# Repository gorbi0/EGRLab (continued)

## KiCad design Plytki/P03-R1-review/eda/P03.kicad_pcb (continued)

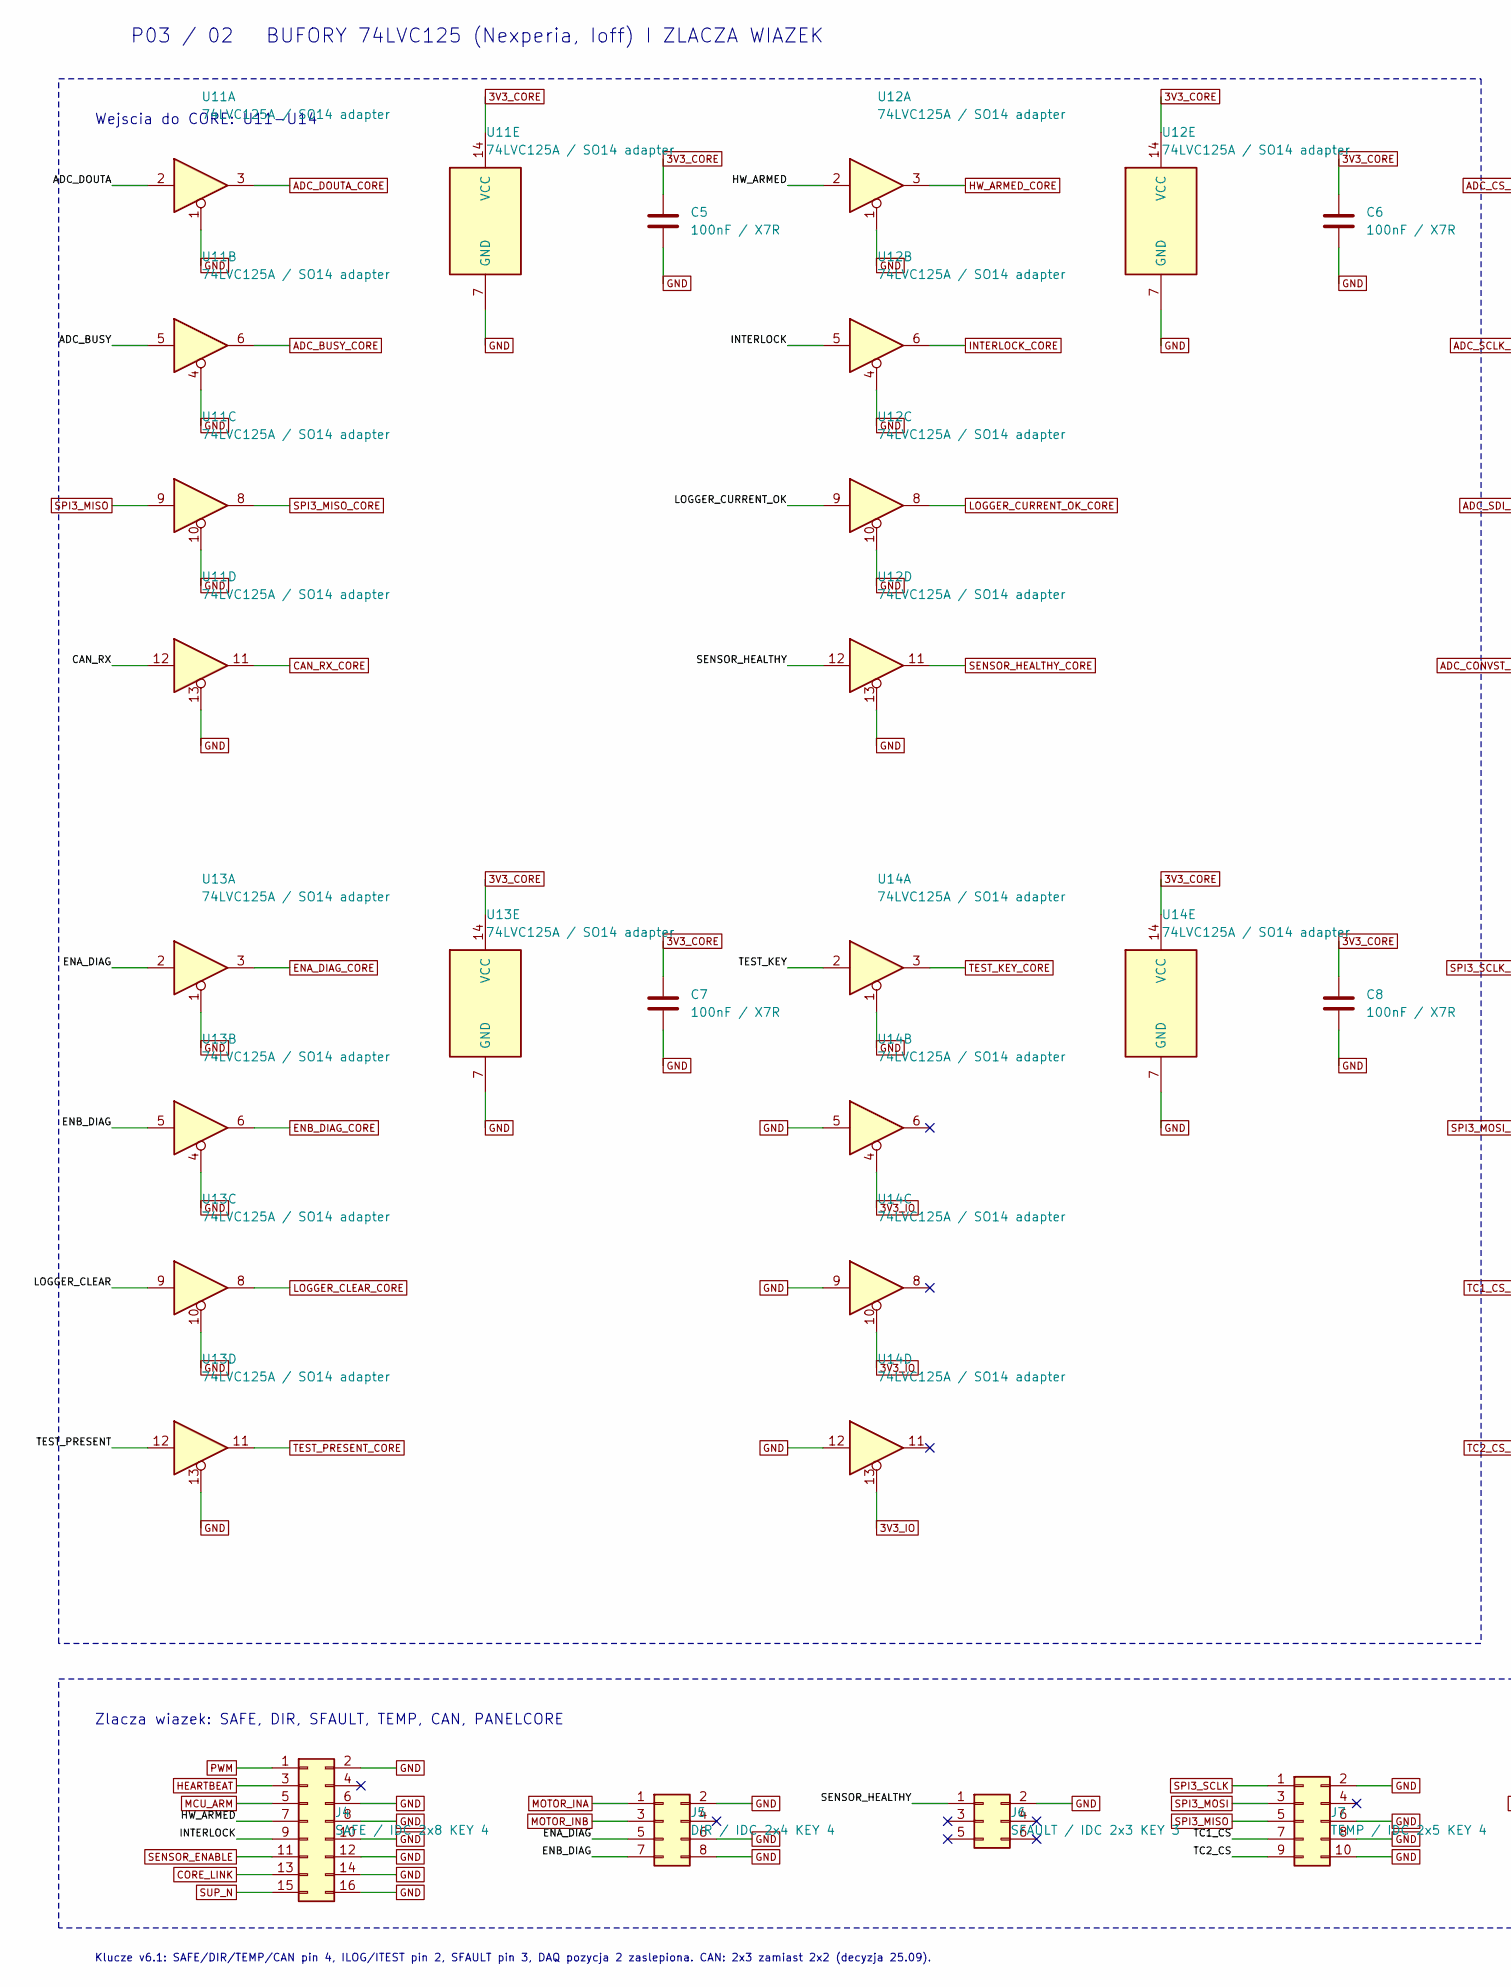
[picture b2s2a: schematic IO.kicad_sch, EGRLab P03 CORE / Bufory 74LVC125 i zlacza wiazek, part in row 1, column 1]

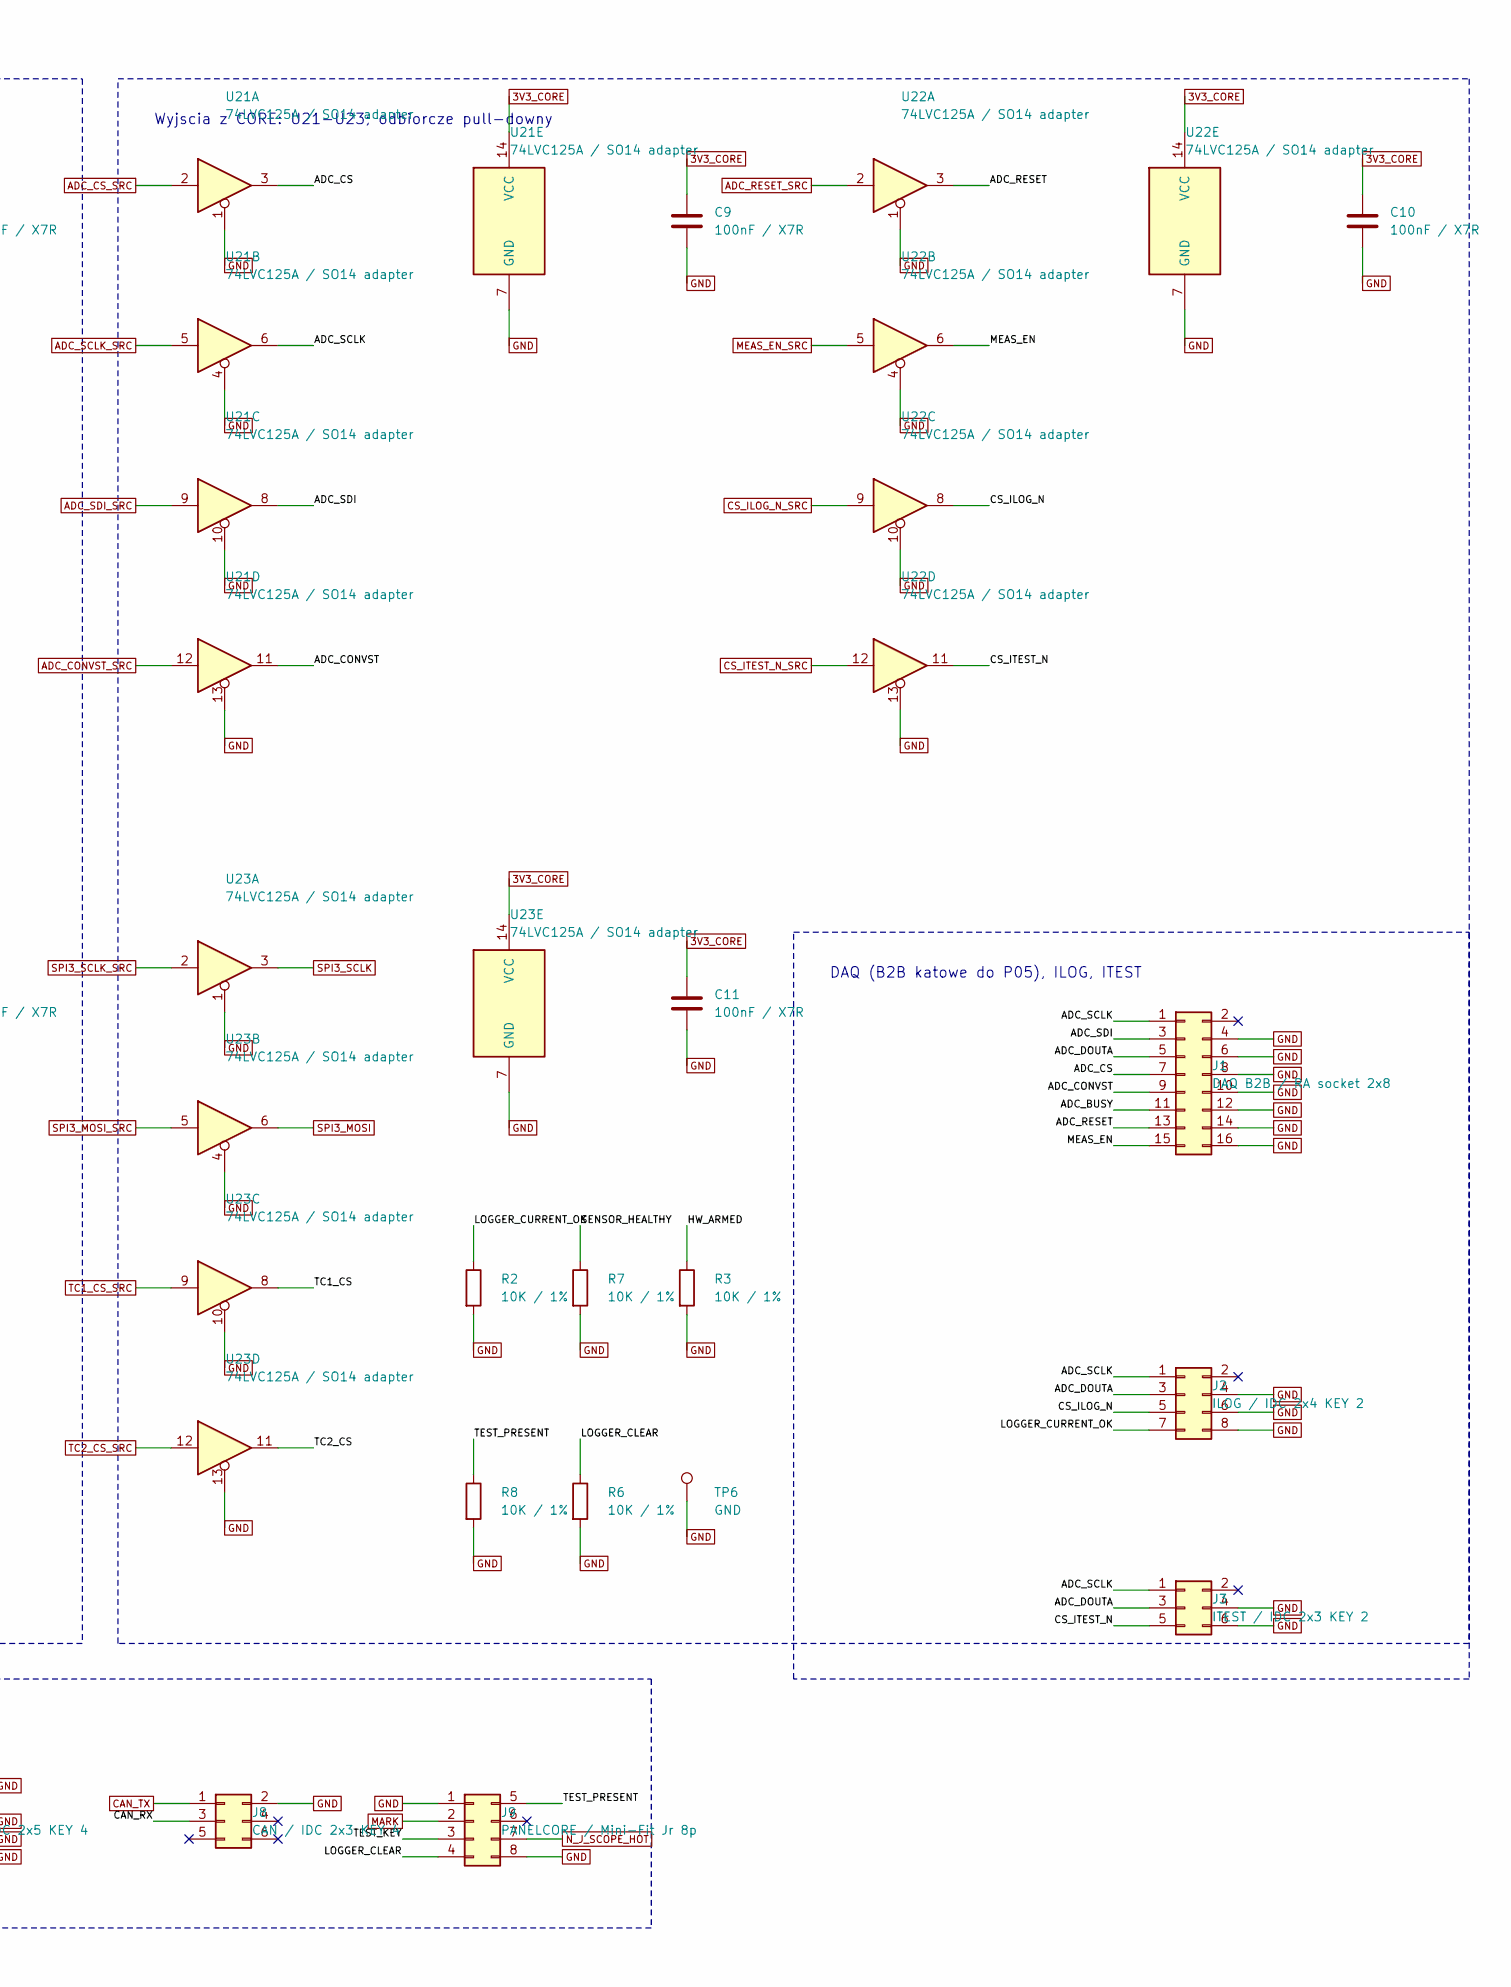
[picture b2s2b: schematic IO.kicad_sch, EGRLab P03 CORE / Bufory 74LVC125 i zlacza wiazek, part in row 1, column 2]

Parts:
C5, C6, C7, C8, C9, C10, C11: 100nF / X7R; C_Vishay_K15_H5_P5; MPN K104K15X7RF53H5
J1: DAQ B2B / RA socket 2x8; PinSocket_2x08_P2.54mm_Horizontal; MPN Samtec SSW-108-02-G-D-RA (right-angle 2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
J2: ILOG / IDC 2x4 KEY 2; IDC-Header_2x04_P2.54mm_Vertical; MPN IDC box header 2x4, 2.54 mm, Au
J3: ITEST / IDC 2x3 KEY 2; IDC-Header_2x03_P2.54mm_Vertical; MPN IDC box header 2x3, 2.54 mm, Au
J4: SAFE / IDC 2x8 KEY 4; IDC-Header_2x08_P2.54mm_Vertical; MPN IDC box header 2x8, 2.54 mm, Au
J5: DIR / IDC 2x4 KEY 4; IDC-Header_2x04_P2.54mm_Vertical; MPN IDC box header 2x4, 2.54 mm, Au
J6: SFAULT / IDC 2x3 KEY 3; IDC-Header_2x03_P2.54mm_Vertical; MPN IDC box header 2x3, 2.54 mm, Au
J7: TEMP / IDC 2x5 KEY 4; IDC-Header_2x05_P2.54mm_Vertical; MPN IDC box header 2x5, 2.54 mm, Au
J8: CAN / IDC 2x3 KEY 4; IDC-Header_2x03_P2.54mm_Vertical; MPN IDC box header 2x3, 2.54 mm, Au
J9: PANELCORE / Mini-Fit Jr 8p; Molex_Mini-Fit_Jr_5566-08A_2x04_P4.20mm_Vertical; MPN Molex Mini-Fit Jr 5566-08A vertical, Au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
R2, R3, R6, R7, R8: 10K / 1%; R_Axial_DIN0207_L6.3mm_D2.5mm_P10.16mm_Horizontal; MPN MF0207FTE-10K
TP6: GND; TestPad_1; MPN PCB test pad
U11, U12, U13, U14, U21, U22, U23: 74LVC125A / SO14 adapter; Adapter_SO14_DIP14_W15.24_Kamami575068; MPN 74LVC125AD,118 (Nexperia) on Kamami 575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

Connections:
3V3_CORE: C5.1, C6.1, C7.1, C8.1, C9.1, C10.1, C11.1, U11.14 (VCC), U12.14 (VCC), U13.14 (VCC), U14.14 (VCC), U21.14 (VCC), U22.14 (VCC), U23.14 (VCC); also elsewhere on the board
3V3_IO: U14.4, U14.10, U14.13; also elsewhere on the board
/IO/ADC_BUSY: J1.11, U11.5
/IO/ADC_CONVST: J1.9, U21.11
/IO/ADC_CS: J1.7, U21.3
/IO/ADC_DOUTA: J1.5, J2.3, J3.3, U11.2
/IO/ADC_RESET: J1.13, U22.3
/IO/ADC_SCLK: J1.1, J2.1, J3.1, U21.6
/IO/ADC_SDI: J1.3, U21.8
/IO/CAN_RX: J8.3, U11.12
/IO/CS_ILOG_N: J2.5, U22.8
/IO/CS_ITEST_N: J3.5, U22.11
/IO/ENA_DIAG: J5.5, U13.2
/IO/ENB_DIAG: J5.7, U13.5
/IO/HW_ARMED: J4.7, R3.1, U12.2
/IO/INTERLOCK: J4.9, U12.5
/IO/LOGGER_CLEAR: J9.4, R6.1, U13.9
/IO/LOGGER_CURRENT_OK: J2.7, R2.1, U12.9
/IO/MEAS_EN: J1.15, U22.6
/IO/SENSOR_HEALTHY: J6.1, R7.1, U12.12
/IO/TC1_CS: J7.7, U23.8
/IO/TC2_CS: J7.9, U23.11
/IO/TEST_KEY: J9.3, U14.2
/IO/TEST_PRESENT: J9.5, R8.1, U13.12
ADC_BUSY_CORE: U11.6; also elsewhere on the board
ADC_CONVST_SRC: U21.12; also elsewhere on the board
ADC_CS_SRC: U21.2; also elsewhere on the board
ADC_DOUTA_CORE: U11.3; also elsewhere on the board
ADC_RESET_SRC: U22.2; also elsewhere on the board
ADC_SCLK_SRC: U21.5; also elsewhere on the board
ADC_SDI_SRC: U21.9; also elsewhere on the board
CAN_RX_CORE: U11.11; also elsewhere on the board
CAN_TX: J8.1; also elsewhere on the board
CORE_LINK: J4.13; also elsewhere on the board
CS_ILOG_N_SRC: U22.9; also elsewhere on the board
CS_ITEST_N_SRC: U22.12; also elsewhere on the board
ENA_DIAG_CORE: U13.3; also elsewhere on the board
ENB_DIAG_CORE: U13.6; also elsewhere on the board
GND: C5.2, C6.2, C7.2, C8.2, C9.2, C10.2, C11.2, J1.4, J1.6, J1.8, J1.10, J1.12, J1.14, J1.16, J2.4, J2.6, J2.8, J3.4, J3.6, J4.2, J4.6, J4.8, J4.10, J4.12, J4.14, J4.16, J5.2, J5.6, J5.8, J6.2, J7.2, J7.6, J7.8, J7.10, J8.2, J9.1, J9.8, R2.2, R3.2, R6.2, R7.2, R8.2, TP6.1, U11.1, U11.4, U11.7 (GND), U11.10, U11.13, U12.1, U12.4, U12.7 (GND), U12.10, U12.13, U13.1, U13.4, U13.7 (GND), U13.10, U13.13, U14.1, U14.5, U14.7 (GND), U14.9, U14.12, U21.1, U21.4, U21.7 (GND), U21.10, U21.13, U22.1, U22.4, U22.7 (GND), U22.10, U22.13, U23.1, U23.4, U23.7 (GND), U23.10, U23.13; also elsewhere on the board
HEARTBEAT: J4.3; also elsewhere on the board
HW_ARMED_CORE: U12.3; also elsewhere on the board
INTERLOCK_CORE: U12.6; also elsewhere on the board
LOGGER_CLEAR_CORE: U13.8; also elsewhere on the board
LOGGER_CURRENT_OK_CORE: U12.8; also elsewhere on the board
MARK: J9.2; also elsewhere on the board
MCU_ARM: J4.5; also elsewhere on the board
MEAS_EN_SRC: U22.5; also elsewhere on the board
MOTOR_INA: J5.1; also elsewhere on the board
MOTOR_INB: J5.3; also elsewhere on the board
N_J_SCOPE_HOT: J9.7; also elsewhere on the board
PWM: J4.1; also elsewhere on the board
SENSOR_ENABLE: J4.11; also elsewhere on the board
SENSOR_HEALTHY_CORE: U12.11; also elsewhere on the board
SPI3_MISO: J7.5, U11.9; also elsewhere on the board
SPI3_MISO_CORE: U11.8; also elsewhere on the board
SPI3_MOSI: J7.3, U23.6; also elsewhere on the board
SPI3_MOSI_SRC: U23.5; also elsewhere on the board
SPI3_SCLK: J7.1, U23.3; also elsewhere on the board
SPI3_SCLK_SRC: U23.2; also elsewhere on the board
SUP_N: J4.15; also elsewhere on the board
TC1_CS_SRC: U23.9; also elsewhere on the board
TC2_CS_SRC: U23.12; also elsewhere on the board
TEST_KEY_CORE: U14.3; also elsewhere on the board
TEST_PRESENT_CORE: U13.11; also elsewhere on the board

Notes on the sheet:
P03 / 02 BUFORY 74LVC125 (Nexperia, Ioff) I ZLACZA WIAZEK
Wejscia do CORE: U11-U14
Wyjscia z CORE: U21-U23; odbiorcze pull-downy
DAQ (B2B katowe do P05), ILOG, ITEST
Zlacza wiazek: SAFE, DIR, SFAULT, TEMP, CAN, PANELCORE
Klucze v6.1: SAFE/DIR/TEMP/CAN pin 4, ILOG/ITEST pin 2, SFAULT pin 3, DAQ pozycja 2 zaslepiona. CAN: 2x3 zamiast 2x2 (decyzja 25.09).

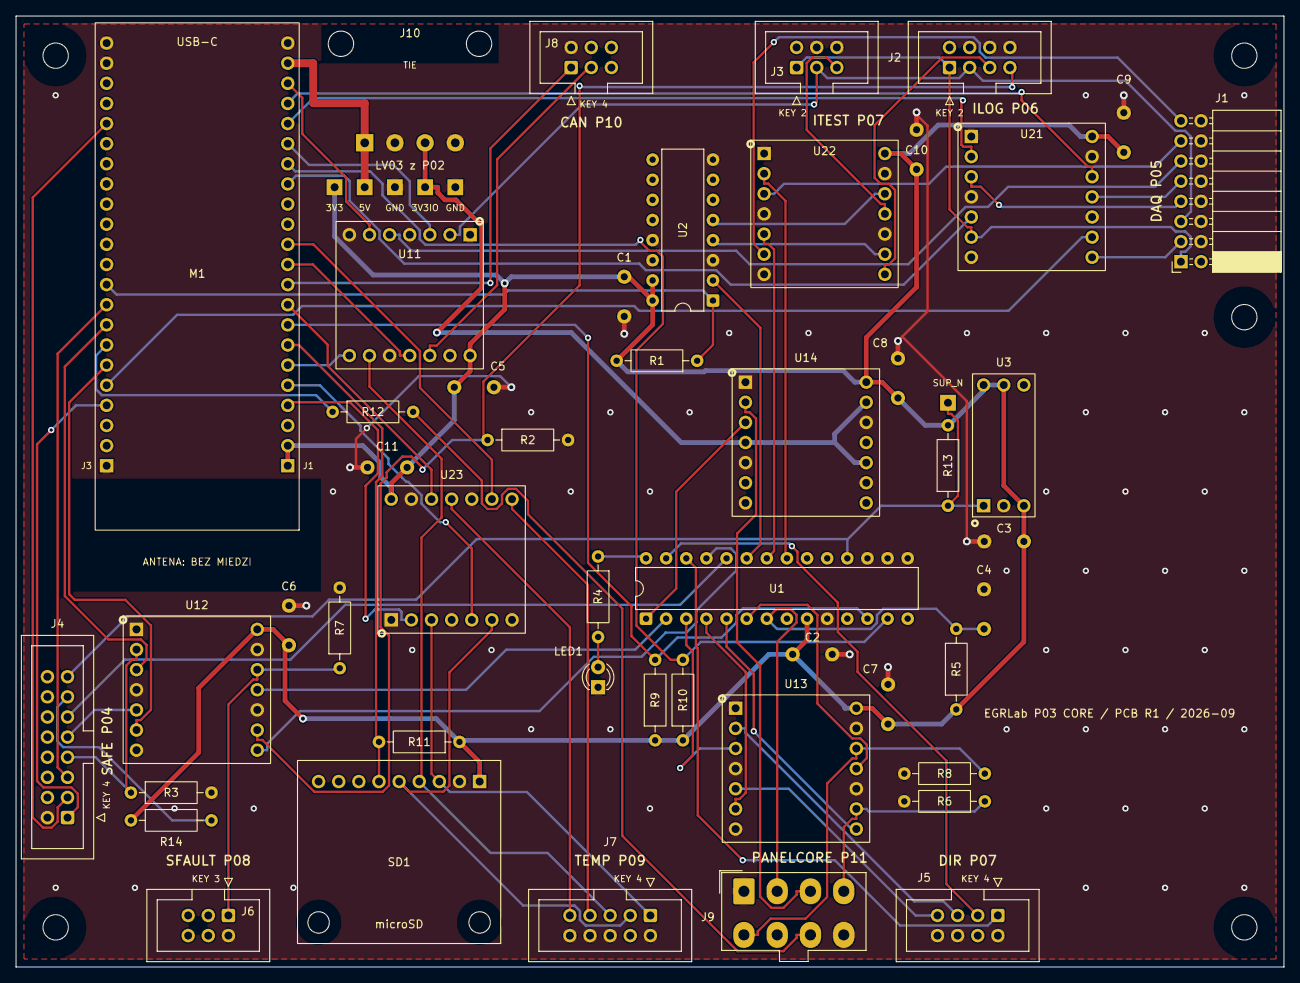
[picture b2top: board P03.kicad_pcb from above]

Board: 2 copper layers, 160.0 x 120.0 mm, 59 parts (0 on the bottom side), 73 nets.

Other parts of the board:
H1, H2, H3, H4, H5: M3 NPTH

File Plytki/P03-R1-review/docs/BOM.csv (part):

ref;source_ref;display;mpn;qty;footprint;url;note
M1;M1;Waveshare ESP32-S3-DEV-KIT-N32R16V;owned (Waveshare ESP32-S3-DEV-KIT-N32R16V) on 2x 1x22 female headers;1;P03:Waveshare_ESP32-S3-DEV-KIT_2x22_W22.86;https://docs.waveshare.com/ESP32-S3-DEV-KIT-N8R8;"Rows 22.86 mm (measured). GPIO numbers are the v6.1 contract. Remove the on-board RGB LED on GPIO38 (v6.1). GPIO47/48 1.8 V: unused. 3V3 = 3V3_CORE; never tie to 3V3_IO."
SD1;SD1;Adafruit 4682 microSD (3V);Adafruit 4682 on a 1x9 female header + 2x M2.5 spacer;1;P03:Adafruit_4682_microSD_1x09;https://www.adafruit.com/product/4682;User decision 25.09: Adafruit 4682 (3 V only, no regulator/level shifter). SO = card out (MISO), SI = card in (MOSI). D1, DAT2, DET unused.
U1;U17;MCP23017-E/SP;MCP23017-E/SP;1;Package_DIP:DIP-28_W7.62mm;https://ww1.microchip.com/downloads/en/devicedoc/20001952c.pdf;Address 0x20 (A2..A0 = GND). IODIRA 0x10, IODIRB 0x7F (v6.1). In 2x DIP14 precision sockets end to end (bought).
C2;C_DEC_U17_9;100nF / X7R;K104K15X7RF53H5;1;P03:C_Vishay_K15_H5_P5;https://www.vishay.com/docs/45171/kseries.pdf;At U1 pin 9.
U2;U_CS;SN74HC139N;SN74HC139N;1;Package_DIP:DIP-16_W7.62mm;https://www.ti.com/lit/ds/symlink/sn74hc139.pdf;/G = GPIO38, A = MEAS_BANK, B = GND (v6.1). Second half disabled. DIP16 socket (bought).
C1;C_CS;100nF / X7R;K104K15X7RF53H5;1;P03:C_Vishay_K15_H5_P5;https://www.vishay.com/docs/45171/kseries.pdf;At U2 pin 16.
R1;R_CS_IDLE;10K / 1%;MF0207FTE-10K;1;Resistor_THT:R_Axial_DIN0207_L6.3mm_D2.5mm_P10.16mm_Horizontal;https://www.yageo.com/upload/media/product/productsearch/dat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;Decoder disabled while GPIO38 floats.
U3;U5;TPS3808G33DBVR / PA0085;TPS3808G33DBVR on Chip Quik PA0085;1;P03:Adapter_SOT23-6_DIP6_W15.24_ChipQuik_PA0085;https://www.ti.com/lit/ds/symlink/tps3808.pdf;SOT23-6 on PA0085 (rows 15.24 mm, measured). Pin n = SOT pin n: confirm on the adapter before soldering. CT open = fixed delay.
C3;C_DEC_U5_6;100nF / X7R;K104K15X7RF53H5;1;P03:C_Vishay_K15_H5_P5;https://www.vishay.com/docs/45171/kseries.pdf;At U3 pin 6.
R13;R_SUP_PU;10K / 1%;MF0207FTE-10K;1;Resistor_THT:R_Axial_DIN0207_L6.3mm_D2.5mm_P10.16mm_Horizontal;https://www.yageo.com/upload/media/product/productsearch/dat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;Open-drain RESET pull-up.
R9;R_PU_I2C_SCL;4K7 / 1%;MF0207FTE-4K7;1;Resistor_THT:R_Axial_DIN0207_L6.3mm_D2.5mm_P10.16mm_Horizontal;https://www.yageo.com/upload/media/product/productsearch/dat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;
R10;R_PU_I2C_SDA;4K7 / 1%;MF0207FTE-4K7;1;Resistor_THT:R_Axial_DIN0207_L6.3mm_D2.5mm_P10.16mm_Horizontal;https://www.yageo.com/upload/media/product/productsearch/dat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;
R11;R_PU_SD_CS;10K / 1%;MF0207FTE-10K;1;Resistor_THT:R_Axial_DIN0207_L6.3mm_D2.5mm_P10.16mm_Horizontal;https://www.yageo.com/upload/media/product/productsearch/dat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;Card deselected while GPIO7 floats.
R12;R_SCOPE;330R / 1%;MF0207FTE-330R;1;Resistor_THT:R_Axial_DIN0207_L6.3mm_D2.5mm_P10.16mm_Horizontal;https://www.yageo.com/upload/media/product/productsearch/dat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;SCOPE_TRIG series resistor to PANELCORE pin 7.
R5;R_MARK;10K / 1%;MF0207FTE-10K;1;Resistor_THT:R_Axial_DIN0207_L6.3mm_D2.5mm_P10.16mm_Horizontal;https://www.yageo.com/upload/media/product/productsearch/dat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;
C4;C_MARK;100nF / X7R;K104K15X7RF53H5;1;P03:C_Vishay_K15_H5_P5;https://www.vishay.com/docs/45171/kseries.pdf;MARK button debounce.
R4;R_LED;1K / 1%;MF0207FTE-1K;1;Resistor_THT:R_Axial_DIN0207_L6.3mm_D2.5mm_P10.16mm_Horizontal;https://www.yageo.com/upload/media/product/productsearch/dat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;
LED1;LED1;GREEN 3mm / STATUS;L-934GD;1;LED_THT:LED_D3.0mm;https://www.kingbrightusa.com/images/catalog/SPEC/L-934GD.pdf;MCP23017 GPA7.
R14;W_LINK;0R;ZOR-25-R-52-0R (or wire link);1;Resistor_THT:R_Axial_DIN0207_L6.3mm_D2.5mm_P10.16mm_Horizontal;https://www.yageo.com/upload/media/product/productsearch/dat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;CORE_LINK = presence of 3V3_CORE (v6.1 W_LINK).
J10;J_LV03B;LV03 / soldered harness;"PCB termination; H_LV03 from P02 J3";1;P03:Pigtail_LV_4xAWG22_P3.81;;H_LV03: 4 x AWG22, 200 mm, Mini-Fit Jr 4p at P02 (LV03). Soldered here, anchor 12.5 mm (v6.1: soldered end on P03).
U11;U_IN1;74LVC125A / SO14 adapter;74LVC125AD,118 (Nexperia) on Kamami 575068;1;P03:Adapter_SO14_DIP14_W15.24_Kamami575068;https://assets.nexperia.com/documents/data-sheet/74LVC125A.pdf;Nexperia only (Ioff), v6.1.
C5;C_U_IN1;100nF / X7R;K104K15X7RF53H5;1;P03:C_Vishay_K15_H5_P5;https://www.vishay.com/docs/45171/kseries.pdf;At U11 pin 14.
U12;U_IN2;74LVC125A / SO14 adapter;74LVC125AD,118 (Nexperia) on Kamami 575068;1;P03:Adapter_SO14_DIP14_W15.24_Kamami575068;https://assets.nexperia.com/documents/data-sheet/74LVC125A.pdf;Nexperia only (Ioff), v6.1.
C6;C_U_IN2;100nF / X7R;K104K15X7RF53H5;1;P03:C_Vishay_K15_H5_P5;https://www.vishay.com/docs/45171/kseries.pdf;At U12 pin 14.
U13;U_IN3;74LVC125A / SO14 adapter;74LVC125AD,118 (Nexperia) on Kamami 575068;1;P03:Adapter_SO14_DIP14_W15.24_Kamami575068;https://assets.nexperia.com/documents/data-sheet/74LVC125A.pdf;Nexperia only (Ioff), v6.1.
C7;C_U_IN3;100nF / X7R;K104K15X7RF53H5;1;P03:C_Vishay_K15_H5_P5;https://www.vishay.com/docs/45171/kseries.pdf;At U13 pin 14.
U14;U_IN4;74LVC125A / SO14 adapter;74LVC125AD,118 (Nexperia) on Kamami 575068;1;P03:Adapter_SO14_DIP14_W15.24_Kamami575068;https://assets.nexperia.com/documents/data-sheet/74LVC125A.pdf;Nexperia only (Ioff), v6.1. Unused OE# = 3V3_IO in U_IN4 as in v6.1.
C8;C_U_IN4;100nF / X7R;K104K15X7RF53H5;1;P03:C_Vishay_K15_H5_P5;https://www.vishay.com/docs/45171/kseries.pdf;At U14 pin 14.
U21;U_OUT1;74LVC125A / SO14 adapter;74LVC125AD,118 (Nexperia) on Kamami 575068;1;P03:Adapter_SO14_DIP14_W15.24_Kamami575068;https://assets.nexperia.com/documents/data-sheet/74LVC125A.pdf;Nexperia only (Ioff), v6.1.
C9;C_U_OUT1;100nF / X7R;K104K15X7RF53H5;1;P03:C_Vishay_K15_H5_P5;https://www.vishay.com/docs/45171/kseries.pdf;At U21 pin 14.
U22;U_OUT2;74LVC125A / SO14 adapter;74LVC125AD,118 (Nexperia) on Kamami 575068;1;P03:Adapter_SO14_DIP14_W15.24_Kamami575068;https://assets.nexperia.com/documents/data-sheet/74LVC125A.pdf;Nexperia only (Ioff), v6.1.
C10;C_U_OUT2;100nF / X7R;K104K15X7RF53H5;1;P03:C_Vishay_K15_H5_P5;https://www.vishay.com/docs/45171/kseries.pdf;At U22 pin 14.
U23;U_OUT3;74LVC125A / SO14 adapter;74LVC125AD,118 (Nexperia) on Kamami 575068;1;P03:Adapter_SO14_DIP14_W15.24_Kamami575068;https://assets.nexperia.com/documents/data-sheet/74LVC125A.pdf;Nexperia only (Ioff), v6.1.
C11;C_U_OUT3;100nF / X7R;K104K15X7RF53H5;1;P03:C_Vishay_K15_H5_P5;https://www.vishay.com/docs/45171/kseries.pdf;At U23 pin 14.
R2;R_CURRENT_OK;10K / 1%;MF0207FTE-10K;1;Resistor_THT:R_Axial_DIN0207_L6.3mm_D2.5mm_P10.16mm_Horizontal;https://www.yageo.com/upload/media/product/productsearch/dat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;Receiver pull-down: open cable = not OK.
R3;R_HW_PD;10K / 1%;MF0207FTE-10K;1;Resistor_THT:R_Axial_DIN0207_L6.3mm_D2.5mm_P10.16mm_Horizontal;https://www.yageo.com/upload/media/product/productsearch/dat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;Receiver pull-down.
R6;R_PD_LOGGER_CLEAR;10K / 1%;MF0207FTE-10K;1;Resistor_THT:R_Axial_DIN0207_L6.3mm_D2.5mm_P10.16mm_Horizontal;https://www.yageo.com/upload/media/product/productsearch/dat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;Receiver pull-down.
R7;R_PD_SENSOR_HEALTHY;10K / 1%;MF0207FTE-10K;1;Resistor_THT:R_Axial_DIN0207_L6.3mm_D2.5mm_P10.16mm_Horizontal;https://www.yageo.com/upload/media/product/productsearch/dat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;Receiver pull-down: cable open or transmitter unpowered = fault (v6.1).
R8;R_PD_TEST_PRESENT;10K / 1%;MF0207FTE-10K;1;Resistor_THT:R_Axial_DIN0207_L6.3mm_D2.5mm_P10.16mm_Horizontal;https://www.yageo.com/upload/media/product/productsearch/dat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;Receiver pull-down.
J1;J_DAQA;DAQ B2B / RA socket 2x8;Samtec SSW-108-02-G-D-RA (right-angle 2x8 socket, Au) or equivalent;1;Connector_PinSocket_2.54mm:PinSocket_2x08_P2.54mm_Horizontal;https://www.samtec.com/products/ssw;User decision 25.09: P05 beside P03, right-angle pair edge to edge. Key: position 2 blocked here, pin 2 removed on P05 (v6.1).
J2;J_ILOGA;ILOG / IDC 2x4 KEY 2;IDC box header 2x4, 2.54 mm, Au;1;Connector_IDC:IDC-Header_2x04_P2.54mm_Vertical;;KEY 2: remove header pin 2 (v6.1).
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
